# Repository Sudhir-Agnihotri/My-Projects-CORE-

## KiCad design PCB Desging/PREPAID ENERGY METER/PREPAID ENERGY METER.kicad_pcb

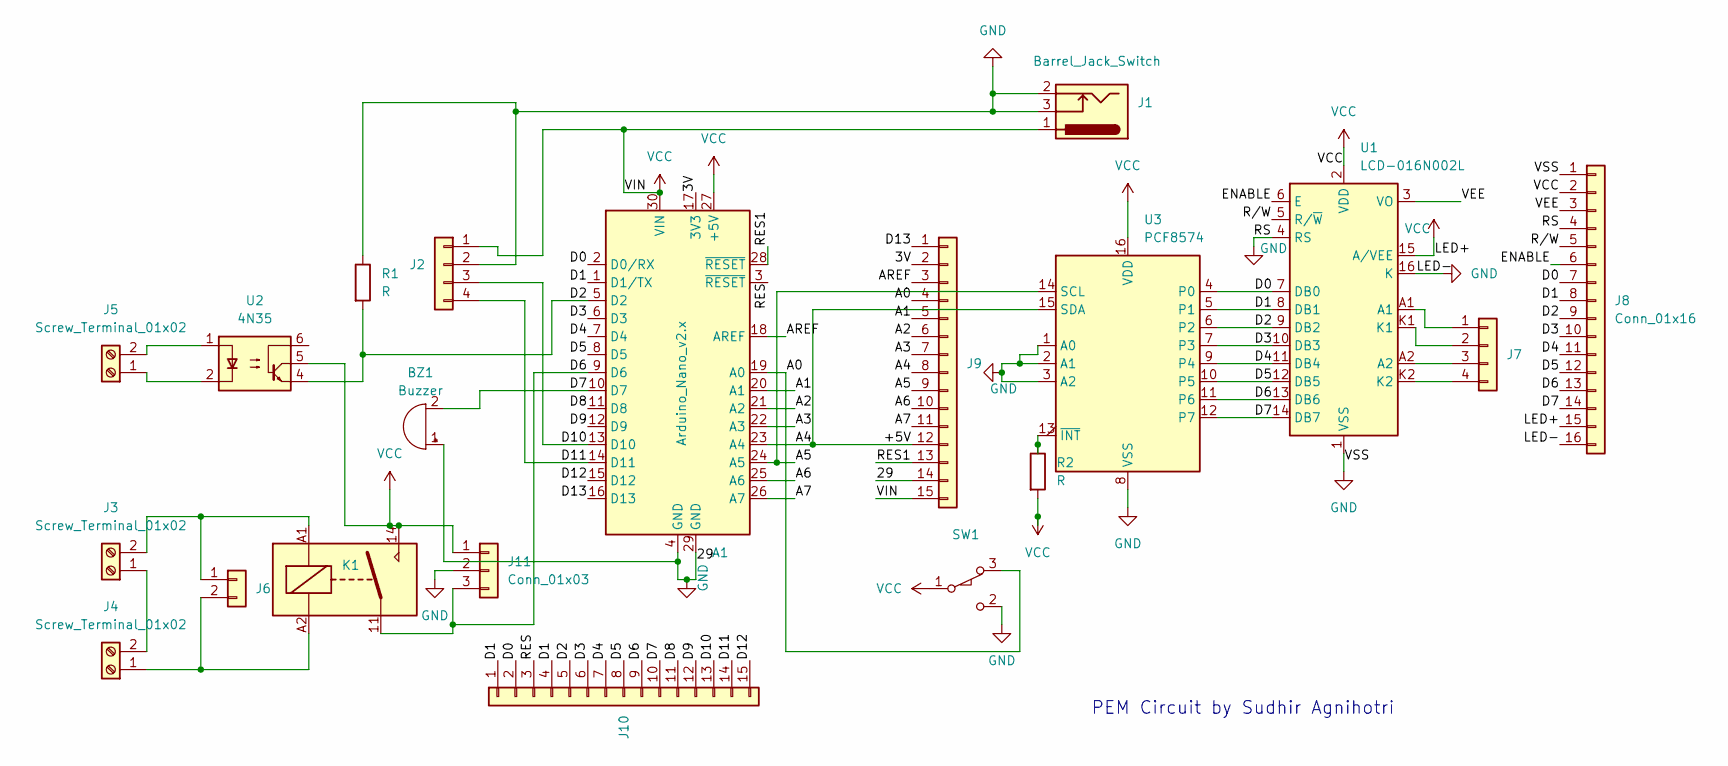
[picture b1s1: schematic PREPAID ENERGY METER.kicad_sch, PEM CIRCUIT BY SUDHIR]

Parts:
A1: Arduino_Nano_v2.x; Arduino_Nano_WithMountingHoles
BZ1: Buzzer; Buzzer_12x9.5RM7.6
J1: Barrel_Jack_Switch; BarrelJack_Horizontal
J2: Conn_01x04; PinHeader_1x04_P2.00mm_Vertical
J3, J4: Screw_Terminal_01x02; TerminalBlock_Phoenix_MPT-0,5-2-2.54_1x02_P2.54mm_Horizontal
J5: Screw_Terminal_01x02; TerminalBlock_Xinya_XY308-2.54-2P_1x02_P2.54mm_Horizontal
J6: Conn_01x02; PinHeader_1x02_P2.54mm_Vertical
J7: Conn_01x04; PinHeader_1x04_P2.54mm_Vertical
J8: Conn_01x16; JST_XH_B16B-XH-A_1x16_P2.50mm_Vertical
J9, J10: Conn_01x15; PinHeader_1x15_P2.54mm_Vertical
J11: Conn_01x03; PinHeader_1x03_P2.54mm_Vertical
K1: Panasonic_ALFG1PF12; Relay_SPST_Panasonic_ALFG_FormA_CircularHoles
R1, R2: R; R_1206_3216Metric
SW1: SW_SPDT_XKB_DMx-xxxx-1; SW_XKB_DM1-16UC-1
U1: LCD-016N002L
U2: 4N35; DIP-6_W7.62mm
U3: PCF8574; DIP-16_W7.62mm_Socket

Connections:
/3V: A1.17 (3V3), J9.2
/+5V: A1.23 (A4), J9.8, J9.12, U3.15 (SDA)
/A0: A1.19 (A0), J9.4, SW1.3 (C)
/A1: A1.20 (A1), J9.5
/A2: A1.21 (A2), J9.6
/A3: A1.22 (A3), J9.7
/A5: A1.24 (A5), J9.9, U3.14 (SCL)
/A6: A1.25 (A6), J9.10
/A7: A1.26 (A7), J9.11
/AREF: A1.18 (AREF), J9.3
/D0: A1.2 (D0/RX), J8.7, J10.2, U1.7 (DB0), U3.4 (P0)
/D1: A1.1 (D1/TX), J8.8, J10.1, J10.4, U1.8 (DB1), U3.5 (P1)
/D2: A1.5 (D2), J8.9, J10.5, R1.2, U1.9 (DB2), U2.4, U3.6 (P2)
/D3: A1.6 (D3), J8.10, J10.6, U1.10 (DB3), U3.7 (P3)
/D4: A1.7 (D4), J8.11, J10.7, U1.11 (DB4), U3.9 (P4)
/D5: A1.8 (D5), J8.12, J10.8, U1.12 (DB5), U3.10 (P5)
/D6: A1.9 (D6), J8.13, J10.9, J11.3, K1.11, U1.13 (DB6), U3.11 (P6)
/D8: A1.11 (D8), J10.11
/D9: A1.12 (D9), J10.12
/D10: A1.13 (D10), J2.3, J10.13
/D11: A1.14 (D11), J2.4, J10.14
/D12: A1.15 (D12), J10.15
/D13: A1.16 (D13), J9.1
/ENABLE: J8.6, U1.6 (E)
/RES: A1.3 (~RESET), J10.3
/RES1: A1.28 (~RESET), J9.13
/R/W: J8.5, U1.5 (R/~W)
/VEE: J8.3, U1.3 (VO)
GND: A1.4 (GND), A1.29 (GND), BZ1.1 (+), J1.2, J1.3, J2.2, J8.1, J8.4, J8.16, J9.14, J11.2, R1.1, SW1.2 (B), U1.1 (VSS), U1.4 (RS), U1.16 (K), U3.1 (A0), U3.2 (A1), U3.3 (A2), U3.8 (VSS)
unnamed: J3.1, J4.2
unnamed: J3.2, J6.1, K1.A1
unnamed: J4.1, J6.2, K1.A2
unnamed: J5.1, U2.2
unnamed: J5.2, U2.1
unnamed: J7.1, U1.A1
unnamed: J7.2, U1.K1
unnamed: J7.3, U1.A2
unnamed: J7.4, U1.K2
unnamed: R2.1, U3.13 (~INT)

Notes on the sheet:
PEM Circuit by Sudhir Agnihotri

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
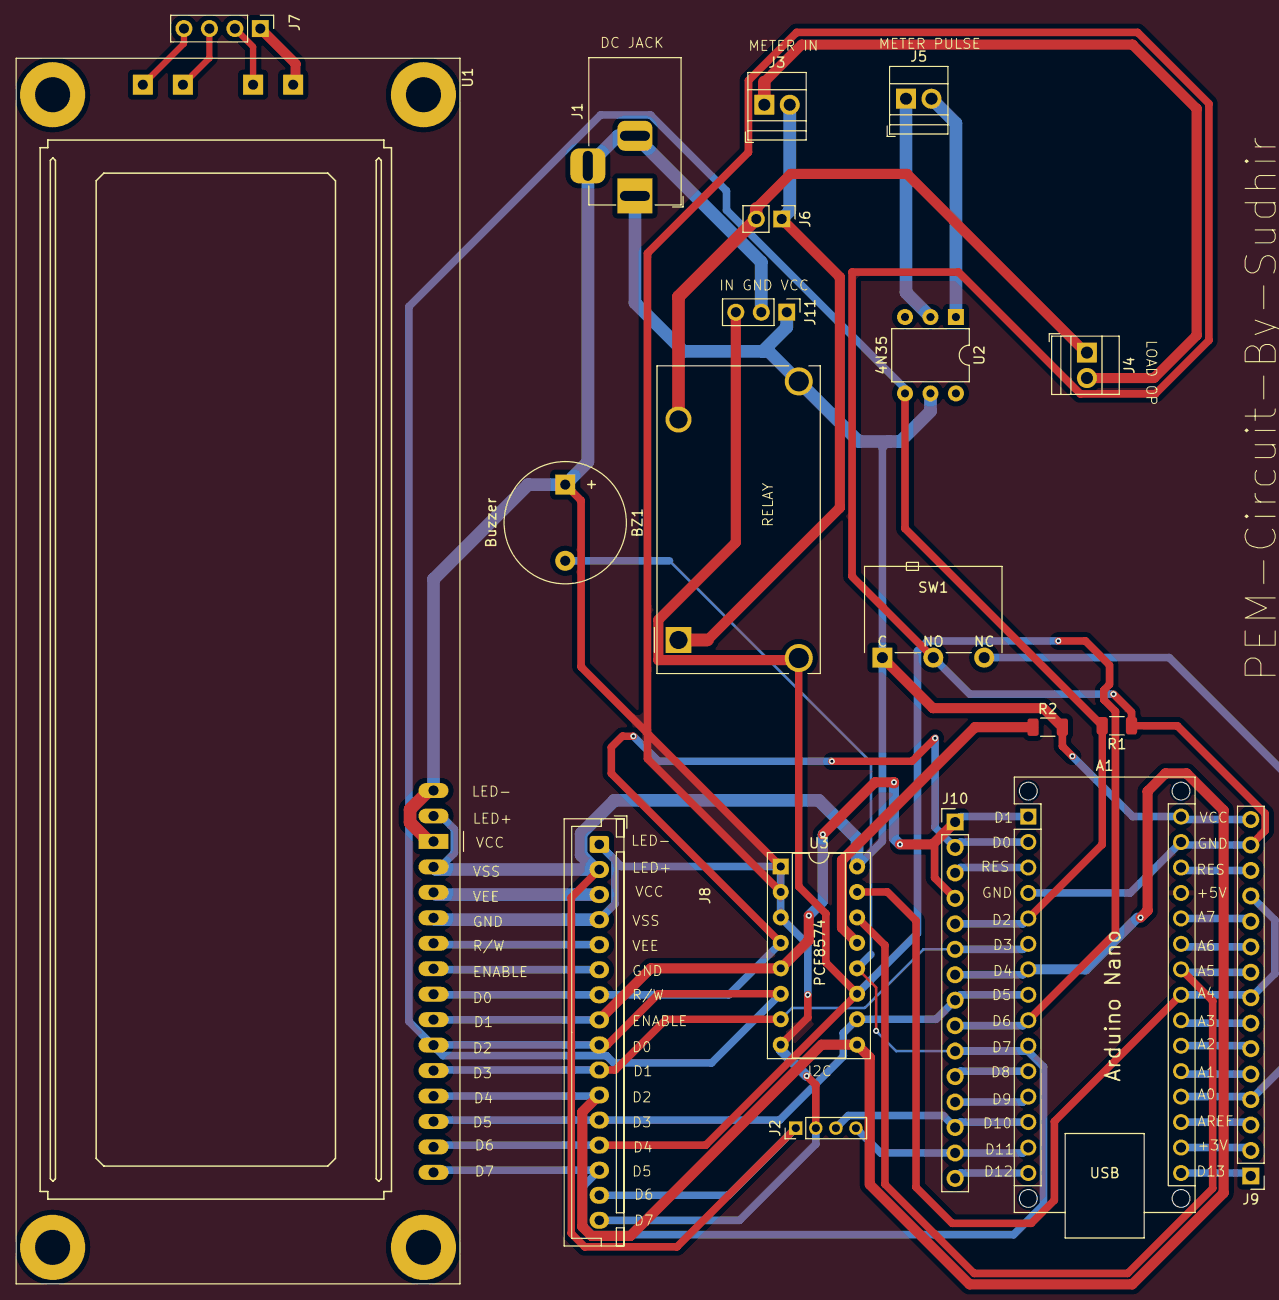
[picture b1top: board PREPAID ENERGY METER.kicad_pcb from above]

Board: 2 copper layers, 20 parts (0 on the bottom side), 40 nets.

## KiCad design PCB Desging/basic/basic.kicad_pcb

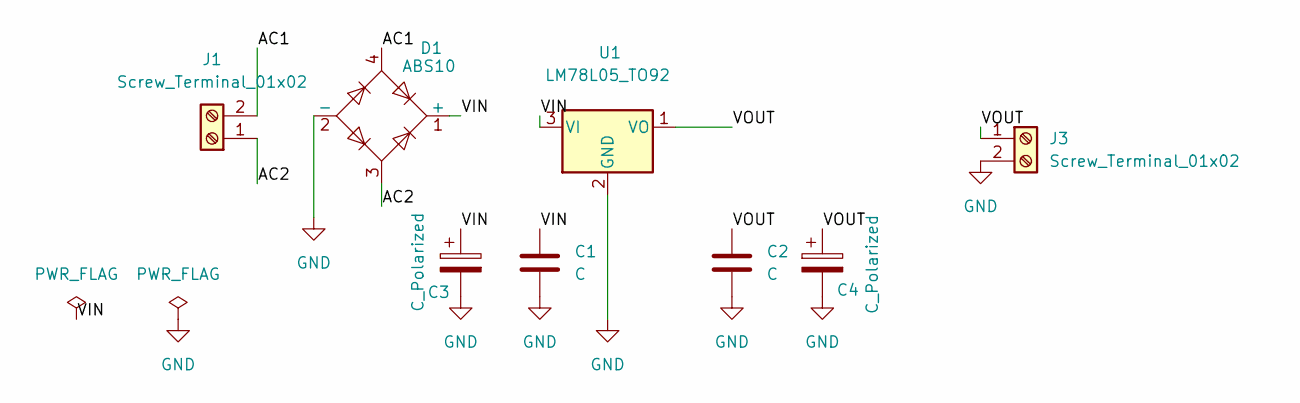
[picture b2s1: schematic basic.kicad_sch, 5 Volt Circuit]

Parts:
C1, C2: C; C_Disc_D7.5mm_W5.0mm_P5.00mm
C3, C4: C_Polarized; CP_Radial_D8.0mm_P5.00mm
D1: ABS10; Diode_Bridge_Vishay_KBL
J1, J3: Screw_Terminal_01x02; TerminalBlock_Phoenix_MKDS-1,5-2_1x02_P5.00mm_Horizontal
U1: LM78L05_TO92; TO-220-3_Vertical

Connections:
/AC1: D1.4, J1.2
/AC2: D1.3, J1.1
/VIN: C1.1, C3.1, D1.1 (+), U1.3 (VI)
/VOUT: C2.1, C4.1, J3.1, U1.1 (VO)
GND: C1.2, C2.2, C3.2, C4.2, D1.2 (-), J3.2, U1.2 (GND)

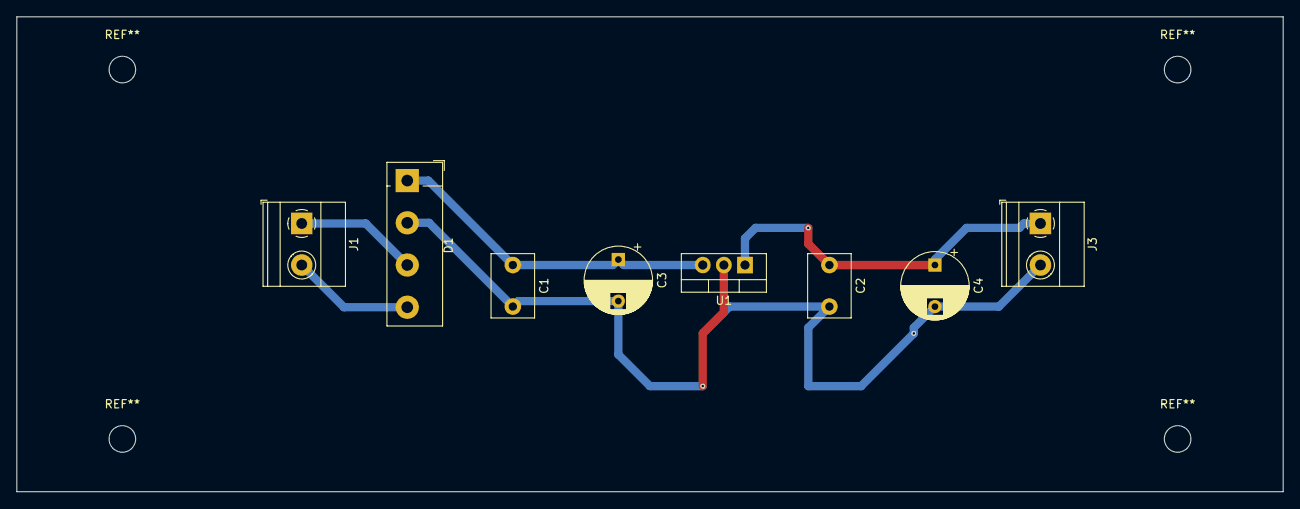
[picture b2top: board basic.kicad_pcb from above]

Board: 2 copper layers, 152.4 x 57.2 mm, 8 parts (0 on the bottom side), 5 nets.

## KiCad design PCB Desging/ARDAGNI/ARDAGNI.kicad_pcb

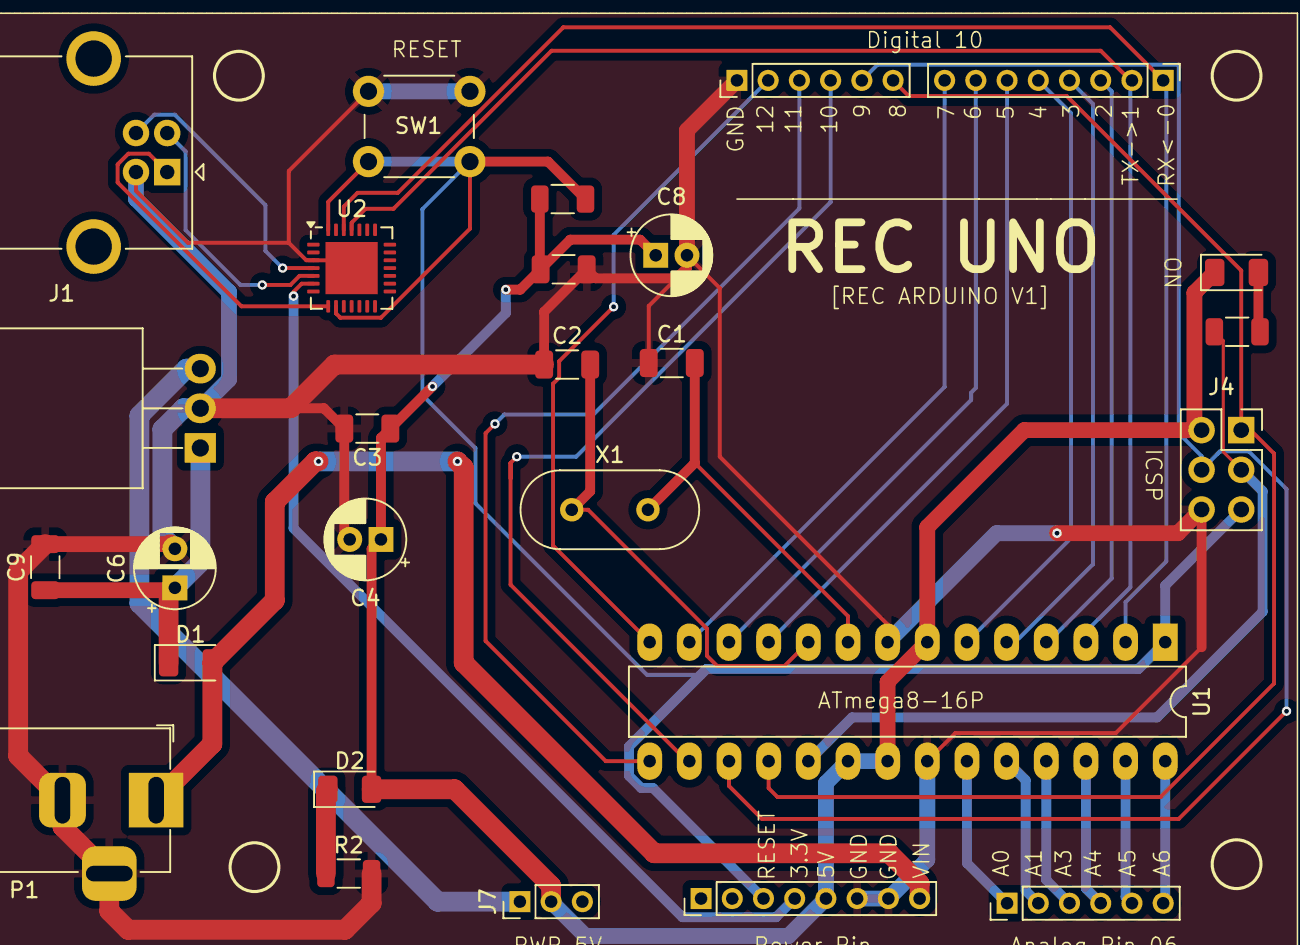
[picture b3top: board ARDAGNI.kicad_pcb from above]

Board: 2 copper layers, 27 parts (0 on the bottom side), 34 nets.

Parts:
C1, C2: C; C_1206_3216Metric
C3, C7: 1uf; C_1206_3216Metric
C4, C8: 10uf; CP_Radial_D5.0mm_P2.00mm
C6: 100uf/25v; CP_Radial_D5.0mm_P2.50mm
C9: 0.1uf; C_1206_3216Metric
D1: 1N4004; D_1206_3216Metric
D2, D3: LED; LED_1206_3216Metric
J1: Analog_6; PinHeader_1x06_P2.00mm_Vertical
J1#2: USB_B; USB_B_OST_USB-B1HSxx_Horizontal
J2: Digital_6; PinHeader_1x06_P2.00mm_Vertical
J3: Digital_10; PinHeader_1x08_P2.00mm_Vertical
J4: ICSP; PinSocket_2x03_P2.54mm_Vertical
J7: Conn_01x03; PinHeader_1x03_P2.00mm_Vertical
J8: POWER; PinHeader_1x08_P2.00mm_Vertical
P1: Barrel_Jack_Switch; BarrelJack_Horizontal
R1, R2: R; R_1206_3216Metric
R3: 470; R_1206_3216Metric
SW1: SW_SPST; SW_PUSH_6mm
U1: ATmega8-16P; DIP-28_W7.62mm_LongPads
U2: CP2102N(USB TO SERIAL); QFN-28-1EP_5x5mm_P0.5mm_EP3.35x3.35mm
U3: LM7805_TO220; TO-220-3_Horizontal_TabDown
X1: 16MHz; Crystal_HC49-4H_Vertical

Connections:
/3.3V: J8.4, U2.6 (VDD)
/5V: J7.1, U3.3 (VO)
/RST: J4.5, J8.3, R1.2, SW1.2 (B), U1.1 (PC6/~RESET), U2.9 (~RST), U2.28 (~DTR)
/RXD: J3.1, U1.2 (PD0), U2.26 (TXD)
/TXD: J3.2, U1.3 (PD1), U2.25 (RXD)
/VIN: D1.2 (A), J8.8, P1.1
GND: C1.1, C2.1, C3.2, C4.2, C6.2, C7.2, C8.2, C9.2, J1#2.4 (GND), J2.1, J4.6, J8.6, J8.7, P1.2, P1.3, R2.2, SW1.1 (A), U1.8 (GND), U1.22 (AGND), U2.3 (GND), U2.29 (GND), U3.2 (GND)
unnamed: C6.1, C9.1, D1.1 (K), U3.1 (VI)
unnamed: D2.1 (K), R2.1
unnamed: D3.2 (A), R3.2
unnamed: J1.1, U1.23 (PC0)
unnamed: J1.2, U1.24 (PC1)
unnamed: J1.3, U1.25 (PC2)
unnamed: J1.4, U1.26 (PC3)
unnamed: J1.5, U1.27 (PC4)
unnamed: J1.6, U1.28 (PC5)
unnamed: J2.2, U1.14 (PB0)
unnamed: J2.3, U1.15 (PB1)
unnamed: J2.4, U1.16 (PB2)
unnamed: J2.5, J4.4, U1.17 (PB3)
unnamed: J2.6, J4.1, U1.18 (PB4)
unnamed: J4.3, R3.1, U1.19 (PB5)
unnamed: J3.3, U1.4 (PD2)
unnamed: J3.4, U1.5 (PD3)
unnamed: J3.5, U1.6 (PD4)
unnamed: J3.6, U1.11 (PD5)
unnamed: J3.7, U1.12 (PD6)
unnamed: J3.8, U1.13 (PD7)
unnamed: J1#2.3 (D+), U2.4 (D+)
unnamed: J1#2.2 (D-), U2.5 (D-)
unnamed: J1#2.1 (VBUS), U2.8 (VBUS)
unnamed: C1.2, U1.9 (PB6/XTAL1), X1.2
unnamed: C2.2, U1.10 (PB7/XTAL2), X1.1
VCC: C3.1, C4.1, C7.1, C8.1, D2.2 (A), D3.1 (K), J4.2, J7.2, J8.5, R1.1, U1.7 (VCC), U1.20 (AVCC), U1.21 (AREF)
